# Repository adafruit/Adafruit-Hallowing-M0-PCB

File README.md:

## Adafruit HalloWing M0 Express PCB

<a href="http://www.adafruit.com/products/3900"><br/>
Click here to purchase one from the Adafruit shop</a>

PCB files for the Adafruit HalloWing M0 Express. Format is EagleCAD schematic and board layout
* https://www.adafruit.com/product/3900

### Description
[This is Hallowing..this is Hallowing... Hallowing! Hallowing!](https://www.youtube.com/watch?v=kGiYxCUAhks&t=39s)
Are you the kind of person who doesn't like taking down the skeletons and spiders until after January? Well, we've got the development board for you. This is electronics at its most spooky! The **Adafruit HalloWing** is a skull-shaped ATSAMD21 board with a ton of extras built in to make for an adorable wearable, badge, development kit, or the engine for your next cosplay or prop.

On the front is a cute **1.44" sized 128x128** full color TFT. Our default example code has our spooky eye demo running but you can use it for anything you like to display in glorious color.

There's also 4 fang-teeth below the display, these are analog/capacitive touch inputs with big alligator-clip holes.

On the reverse is a smorgasbord of electronic goodies:

 * **ATSAMD21G18** @ 48MHz with 3.3V logic/power - 256KB of FLASH + 32KB of RAM
 * **8 MB of SPI Flash** for storing images, sounds, animations, whatever!
 * **3-axis accelerometer** (motion sensor)
 * **Light sensor**, reverse-mount so that it points out the front
 * **Mono Class-D speaker driver** for 4-8 ohm speakers, up to 2 Watts, with mini volume pot
 * LiPoly battery port with built in recharging capability
 * USB port for battery charging, programming and debugging
 * Two female header strips with Feather-compatible pinout so you can plug any FeatherWings in
 * JST ports for Neopixels, sensor input, and I2C (you can fit I2C Grove connectors in here)
 * 3.3V regulator with 500mA peak current output
 * Reset button
 * On-Off switch

**OK so technically it's more like a really tricked-out Feather M0 Express than a Wing but we simply could not resist the Hallowing pun.**

Right now you can use the Hallowing similarly Feather M0 Express, it's got the same chip although the pins have been rearranged. We've got both Arduino and CircuitPython build support for it so you can pick your favorite development language! The extra 8 MB of SPI Flash is great for sound effects projects where you want to play up to 3 minutes of WAV files.

On each side of the Hallowing are JST-PH plugs for connecting external devices. The 3-pin JSTs connect to analog pins on the SAMD21, so you can use them for analog inputs. We label one for Neopixel and one for Sensors since we think most people will have one of each. The 4-pin JST connector connects to the I2C port and you can fit Grove connectors in it for additional hardware support.

**Does not come with a Lipoly battery!** [We recommend our 350mAh](https://www.adafruit.com/product/2750) or [500mAh batteries](https://www.adafruit.com/product/1578) but any 3.7/4.2V Adafruit Lipoly will do the trick.

Comes fully assembled and ready to be your spooky friend. We install the UF2 bootloader on it so updating code and converting it to CircuitPython is easy. [Check out the Adafruit Learn guide for software, libraries, example code, schematics, datasheets and more!](https://learn.adafruit.com/adafruit-hallowing)

### License

Adafruit invests time and resources providing this open source design, please support Adafruit and open-source hardware by purchasing products from [Adafruit](https://www.adafruit.com)!

Designed by Limor Fried/Ladyada for Adafruit Industries.

Creative Commons Attribution/Share-Alike, all text above must be included in any redistribution. See license.txt for additional details.

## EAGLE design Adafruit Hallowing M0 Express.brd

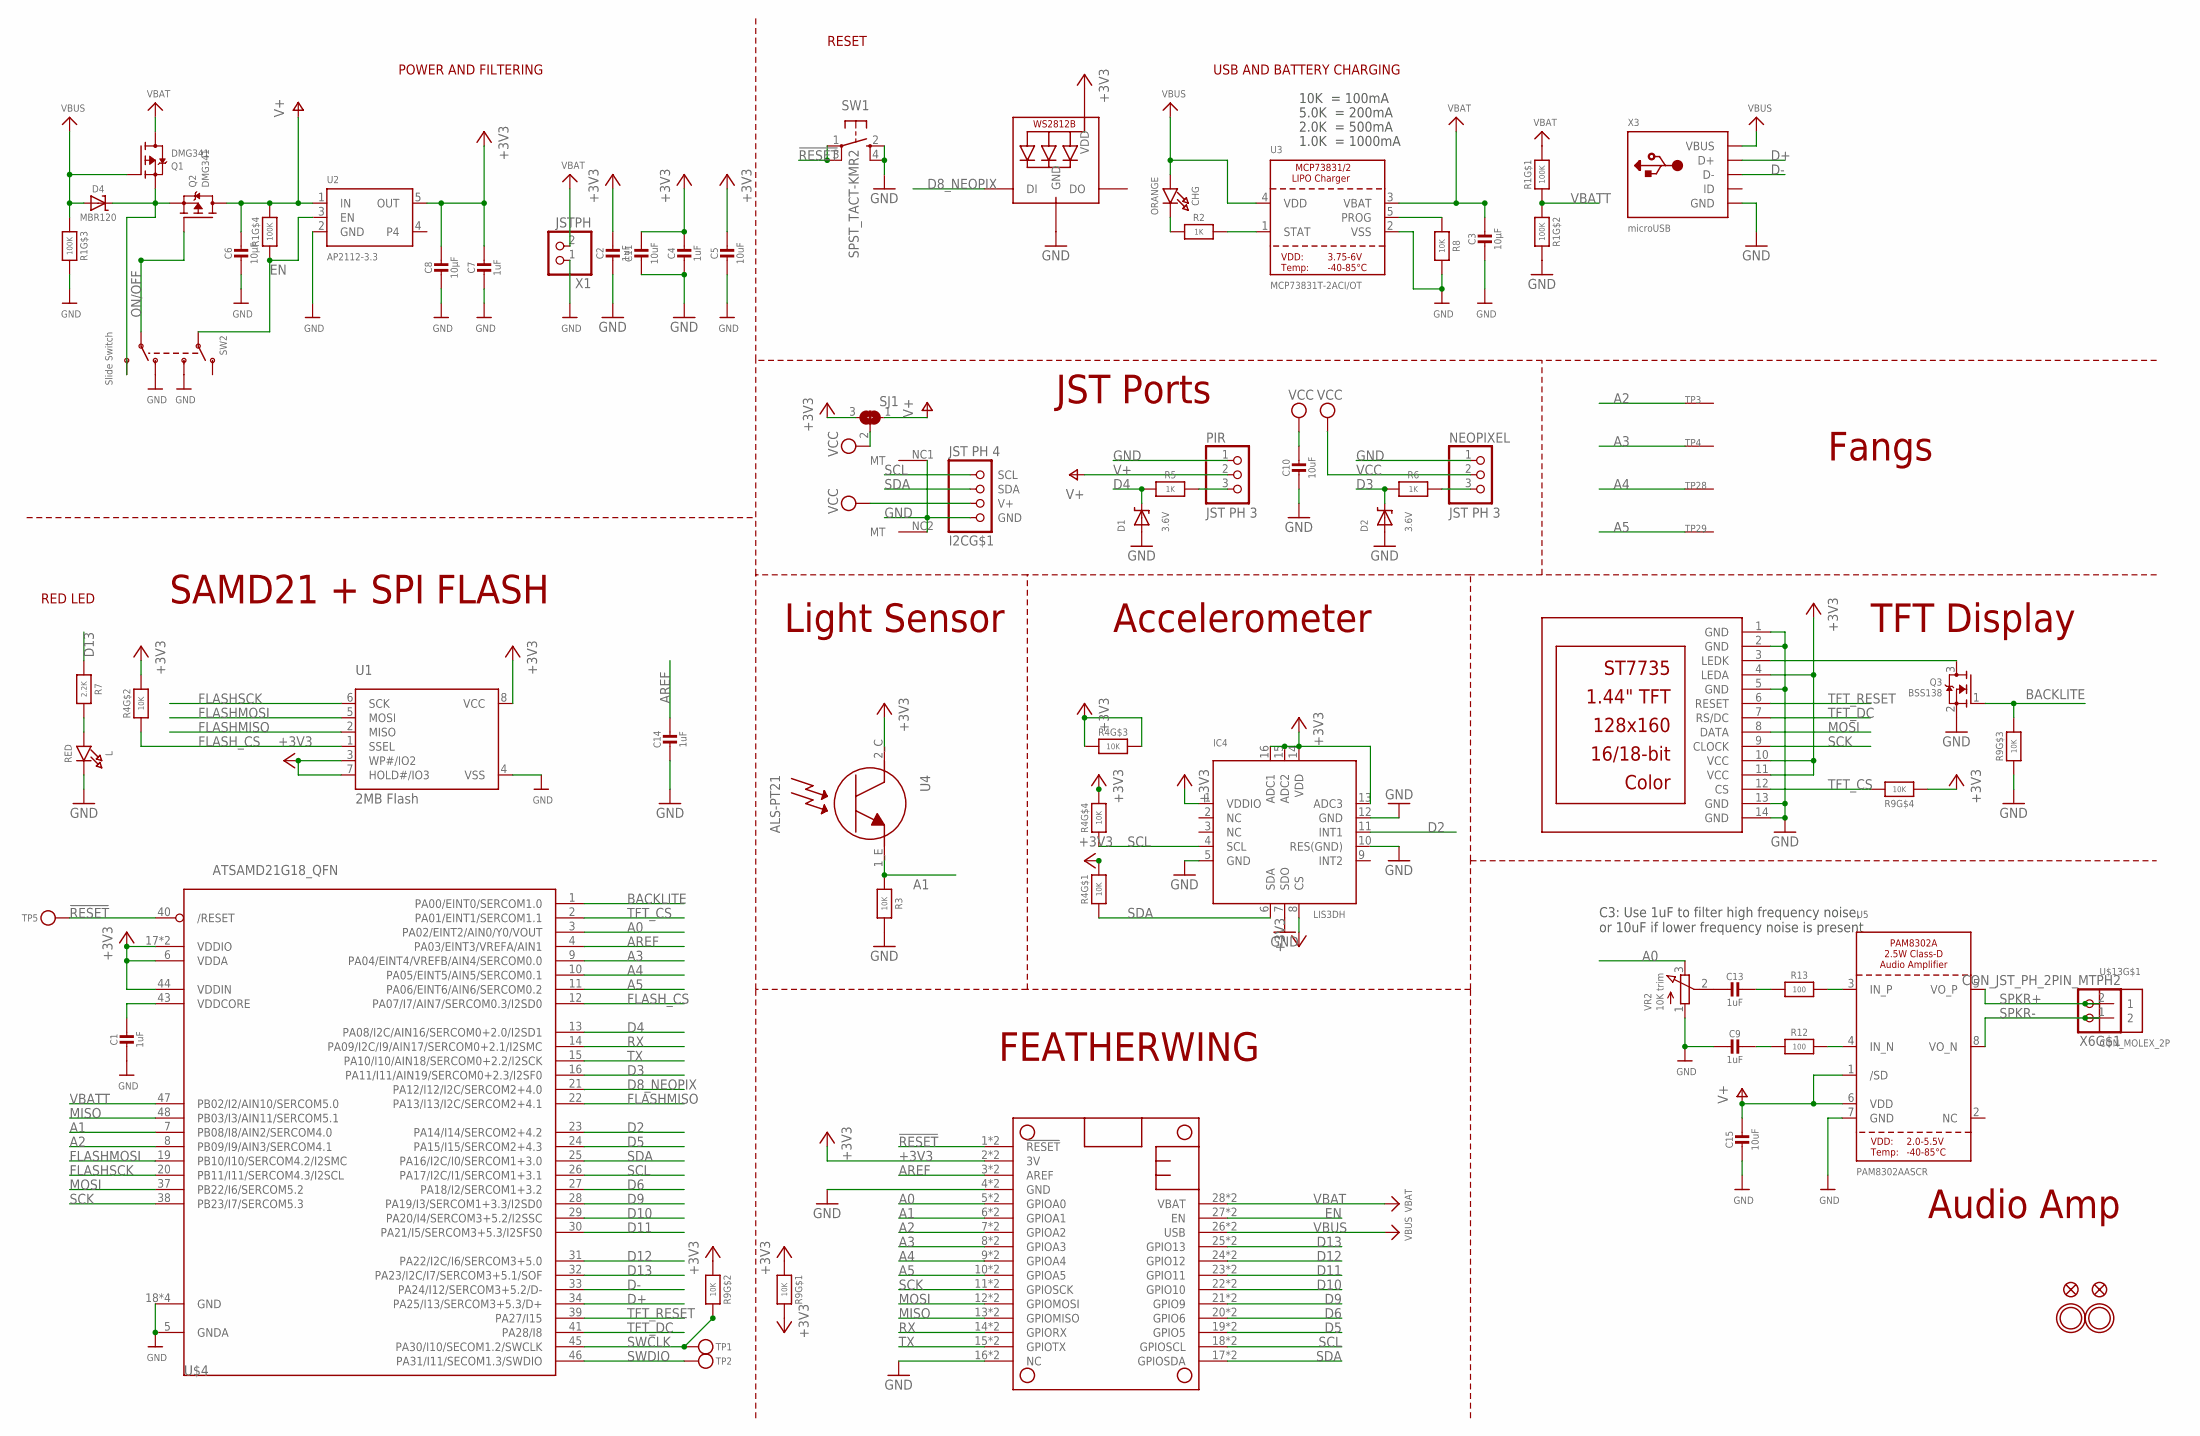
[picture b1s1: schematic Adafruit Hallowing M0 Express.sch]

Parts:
C1, C2, C4, C7, C9, C13, C14: 1uF; 0603-NO
C3, C6: 10µF; 0805-NO
C5, C10, C15: 10uF; 0805-NO
C8: 10µF; 0805_10MGAP
C11: 10uF; 0805_10MGAP
CHG: ORANGE; CHIPLED_0805_NOOUTLINE
D1, D2: 3.6V; SOD-323
D4: MBR120; SOD-123
I2C: JST PH 4; JSTPH4
IC4: LIS3DH; LGA16_3X3MM
L: RED; CHIPLED_0805_NOOUTLINE
LED1: WS2812B3535; LED3535
MS1: FEATHERWING_SMTDUALNOHOLES; FEATHERWING_SMT_NOHOLES
NEOPIXEL: JST PH 3; JSTPH3
PIR: JST PH 3; JSTPH3
Q1, Q2: DMG341; SOT23-R
Q3: BSS138; SOT23-WIDE
R1: 100K; RESPACK_4X0603
R2, R5, R6: 1K; 0603-NO
R3, R8: 10K; 0603-NO
R4, R9: 10K; RESPACK_4X0603
R7: 2.2K; 0603-NO
R12, R13: 100; 0603-NO
SJ1: SOLDERJUMPER_2WAY; SOLDERJUMPER_2WAY_OPEN_NOPASTE
SW1: SPST_TACT-KMR2; KMR2
SW2: Slide Switch; EG1390
TFT: DISP_LCD_ST7735_1.44IN; TFT_1.44IN_128_128
TP1, TP2, TP5: TESTPOINTROUND1.5MM; TESTPOINT_ROUND_1.5MM
TP3, TP29: SEWTAP_ALLILONG; PCB_ALLI_LONG
TP4, TP28: SEWTAPPCB_ALLIGATOR; PCB_ALLI
U1: 2MB Flash; SOIC8_208MIL
U2: AP2112-3.3; SOT23-5
U3: MCP73831T-2ACI/OT; SOT23-5
U4: ALS-PT21; ALS-PT26-21C
U5: PAM8302AASCR; MSOP8_0.65MM
U$4: ATSAMD21G18_QFN; TQFN48_7MM
U$13: CON_MOLEX_2P; 53398-0271
U$31, U$32: MOUNTINGHOLE2.5; MOUNTINGHOLE_2.5_PLATED
U$34, U$35: FIDUCIAL_1MM
VR2: 10K trim; TRIMPOT_BOURNS_3303W
X1: JSTPH; JSTPH2
X3: microUSB; 4UCONN_20329_V2
X6: CON_JST_PH_2PIN_MTPH2; JSTPH2

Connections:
!RESET: MS1.1 (!RESET), MS1.1' (!RESET), SW1.1, SW1.3 (P1), TP5.P$1, U$4.40 (/RESET)
+3V3: C2.1, C4.1, C5.1, C7.1, C8.1, C11.1, IC4.1 (VDDIO), IC4.8 (CS), IC4.13 (ADC3), IC4.14 (VDD), IC4.15 (ADC2), IC4.16 (ADC1), LED1.2 (VDD), MS1.2 (3V), MS1.2' (3V), R4.3 (1), R4.5 (2), R4.6 (2), R4.7 (2), R4.8 (2), R9.1, R9.2 (1), R9.4 (1), R9.8 (2), SJ1.3, TFT.4 (LEDA), TFT.10 (VCC), TFT.11 (VCC), U1.3 (WP#/IO2), U1.7 (HOLD#/IO3), U1.8 (VCC), U2.5 (OUT), U4.2_C (C), U$4.6 (VDDA), U$4.17 (VDDIO), U$4.36 (VDDIO), U$4.44 (VDDIN)
A0: MS1.5 (GPIOA0), MS1.5' (GPIOA0), U$4.3 (PA02/EINT2/AIN0/Y0/VOUT), VR2.3 (E)
A1: MS1.6 (GPIOA1), MS1.6' (GPIOA1), R3.2, U4.1_E (E), U$4.7 (PB08/I8/AIN2/SERCOM4.0)
A2: MS1.7 (GPIOA2), MS1.7' (GPIOA2), TP3.P$1, U$4.8 (PB09/I9/AIN3/SERCOM4.1)
A3: MS1.8 (GPIOA3), MS1.8' (GPIOA3), TP4.P$1, U$4.9 (PA04/EINT4/VREFB/AIN4/SERCOM0.0)
A4: MS1.9 (GPIOA4), MS1.9' (GPIOA4), TP28.P$1, U$4.10 (PA05/EINT5/AIN5/SERCOM0.1)
A5: MS1.10 (GPIOA5), MS1.10' (GPIOA5), TP29.P$1, U$4.11 (PA06/EINT6/AIN6/SERCOM0.2)
AREF: C14.1, MS1.3 (AREF), MS1.3' (AREF), U$4.4 (PA03/EINT3/VREFA/AIN1)
BACKLITE: Q3.1 (G), R9.6 (2), U$4.1 (PA00/EINT0/SERCOM1.0)
CHG_LED: R2.2, U3.1 (STAT)
CHG_RATE: R8.1, U3.5 (PROG)
D2: IC4.11 (INT1), U$4.23 (PA14/I14/SERCOM2+4.2)
D3: D2.C, R6.2, U$4.16 (PA11/I11/AIN19/SERCOM0+2.3/I2SF0)
D4: D1.C, R5.2, U$4.13 (PA08/I2C/AIN16/SERCOM0+2.0/I2SD1)
D5: MS1.19 (GPIO5), MS1.19' (GPIO5), U$4.24 (PA15/I15/SERCOM2+4.3)
D6: MS1.20 (GPIO6), MS1.20' (GPIO6), U$4.27 (PA18/I2/SERCOM1+3.2)
D8_NEOPIX: LED1.1 (DI), U$4.21 (PA12/I12/I2C/SERCOM2+4.0)
D9: MS1.21 (GPIO9), MS1.21' (GPIO9), U$4.28 (PA19/I3/SERCOM1+3.3/I2SD0)
D10: MS1.22 (GPIO10), MS1.22' (GPIO10), U$4.29 (PA20/I4/SERCOM3+5.2/I2SSC)
D11: MS1.23 (GPIO11), MS1.23' (GPIO11), U$4.30 (PA21/I5/SERCOM3+5.3/I2SFS0)
D12: MS1.24 (GPIO12), MS1.24' (GPIO12), U$4.31 (PA22/I2C/I6/SERCOM3+5.0)
D13: MS1.25 (GPIO13), MS1.25' (GPIO13), R7.1, U$4.32 (PA23/I2C/I7/SERCOM3+5.1/SOF)
D+: U$4.34 (PA25/I13/SERCOM3+5.3/D+), X3.D+
D-: U$4.33 (PA24/I12/SERCOM3+5.2/D-), X3.D-
EN: MS1.27 (EN), MS1.27' (EN), R1.4 (1), SW2.P1, U2.3 (EN)
FLASHMISO: U1.2 (MISO), U$4.22 (PA13/I13/I2C/SERCOM2+4.1)
FLASHMOSI: U1.5 (MOSI), U$4.19 (PB10/I10/SERCOM4.2/I2SMC)
FLASHSCK: U1.6 (SCK), U$4.20 (PB11/I11/SERCOM4.3/I2SCL)
FLASH_CS: R4.2 (1), U1.1 (SSEL), U$4.12 (PA07/I7/AIN7/SERCOM0.3/I2SD0)
GND: C1.2, C2.2, C3.2, C4.2, C5.2, C6.2, C7.2, C8.2, C9.2, C10.2, C11.2, C14.2, C15.2, D1.A, D2.A, I2C.1 (GND), I2C.NC1 (MT), I2C.NC2 (MT), IC4.5 (GND), IC4.7 (SDO), IC4.10 (RES(GND)), IC4.12 (GND), L.C, LED1.4 (GND), MS1.4 (GND), MS1.4' (GND), MS1.16 (NC), MS1.16' (NC), NEOPIXEL.1, PIR.1, Q3.2 (S), R1.6 (2), R1.7 (2), R3.1, R8.2, R9.3 (1), SW1.2 (S), SW1.4 (S1), SW2.O2, SW2.S1, TFT.1 (GND), TFT.2 (GND), TFT.5 (GND), TFT.13 (GND), TFT.14 (GND), U1.4 (VSS), U2.2 (GND), U3.2 (VSS), U5.7 (GND), U$4.5 (GNDA), U$4.18 (GND), U$4.35 (GND), U$4.42 (GND), U$4.THERMAL (GND), VR2.1 (A), X1.1, X3.BASE@1 (GND), X3.BASE@2 (GND), X3.GND, X3.SPRT@1 (GND), X3.SPRT@2 (GND), X3.SPRT@3 (GND), X3.SPRT@4 (GND)
MISO: MS1.13 (GPIOMISO), MS1.13' (GPIOMISO), U$4.48 (PB03/I3/AIN11/SERCOM5.1)
MOSI: MS1.12 (GPIOMOSI), MS1.12' (GPIOMOSI), TFT.8 (DATA), U$4.37 (PB22/I6/SERCOM5.2)
unnamed: CHG.C, R2.1
unnamed: L.A, R7.2
unnamed: Q3.3 (D), TFT.3 (LEDK)
unnamed: D4.C, Q1.2 (S), Q2.2 (S), SW2.S2
unnamed: R12.2, U5.4 (IN_N)
unnamed: R13.2, U5.3 (IN_P)
unnamed: C9.1, R12.1
unnamed: C13.1, R13.1
unnamed: C13.2, VR2.2 (S)
NEOPIXELOUT: NEOPIXEL.3, R6.1
ON/OFF: Q2.1 (G), SW2.P2
RX: MS1.14 (GPIORX), MS1.14' (GPIORX), U$4.14 (PA09/I2C/I9/AIN17/SERCOM0+2.1/I2SMC)
SCK: MS1.11 (GPIOSCK), MS1.11' (GPIOSCK), TFT.9 (CLOCK), U$4.38 (PB23/I7/SERCOM5.3)
SCL: I2C.4 (SCL), IC4.4 (SCL), MS1.18 (GPIOSCL), MS1.18' (GPIOSCL), R4.4 (1), U$4.26 (PA17/I2C/I1/SERCOM1+3.1)
SDA: I2C.3 (SDA), IC4.6 (SDA), MS1.17 (GPIOSDA), MS1.17' (GPIOSDA), R4.1, U$4.25 (PA16/I2C/I0/SERCOM1+3.0)
SENSORIN: PIR.3, R5.1
SPKR+: U5.5 (VO_P), U$13.1, X6.2
SPKR-: U5.8 (VO_N), U$13.2, X6.1
SWCLK: R9.7 (2), TP1.P$1, U$4.45 (PA30/I10/SECOM1.2/SWCLK)
SWDIO: TP2.P$1, U$4.46 (PA31/I11/SECOM1.3/SWDIO)
TFT_CS: R9.5 (2), TFT.12 (CS), U$4.2 (PA01/EINT1/SERCOM1.1)
TFT_DC: TFT.7 (RS/DC), U$4.41 (PA28/I8)
TFT_RESET: TFT.6 (RESET), U$4.39 (PA27/I15)
TX: MS1.15 (GPIOTX), MS1.15' (GPIOTX), U$4.15 (PA10/I10/AIN18/SERCOM0+2.2/I2SCK)
V+: C6.1, C15.1, PIR.2, Q2.3 (D), R1.5 (2), SJ1.1, U2.1 (IN), U5.1 (/SD), U5.6 (VDD)
VBAT: C3.1, MS1.28 (VBAT), MS1.28' (VBAT), Q1.3 (D), R1.8 (2), U3.3 (VBAT), X1.2
VBATT: R1.1, R1.2 (1), U$4.47 (PB02/I2/AIN10/SERCOM5.0)
VBUS: CHG.A, D4.A, MS1.26 (USB), MS1.26' (USB), Q1.1 (G), R1.3 (1), U3.4 (VDD), X3.VBUS
VCC: C10.1, I2C.2 (V+), NEOPIXEL.2, SJ1.2
VDDCORE: C1.1, U$4.43 (VDDCORE)

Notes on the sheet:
POWER AND FILTERING
RESET
10K = 100mA
5.0K = 200mA
2.0K = 500mA
1.0K = 1000mA
USB AND BATTERY CHARGING
RED LED
C3: Use 1uF to filter high frequency noise, or 10uF if lower frequency noise is present
Accelerometer
Light Sensor
FEATHERWING
SAMD21 + SPI FLASH
Fangs
TFT Display
Audio Amp
JST Ports

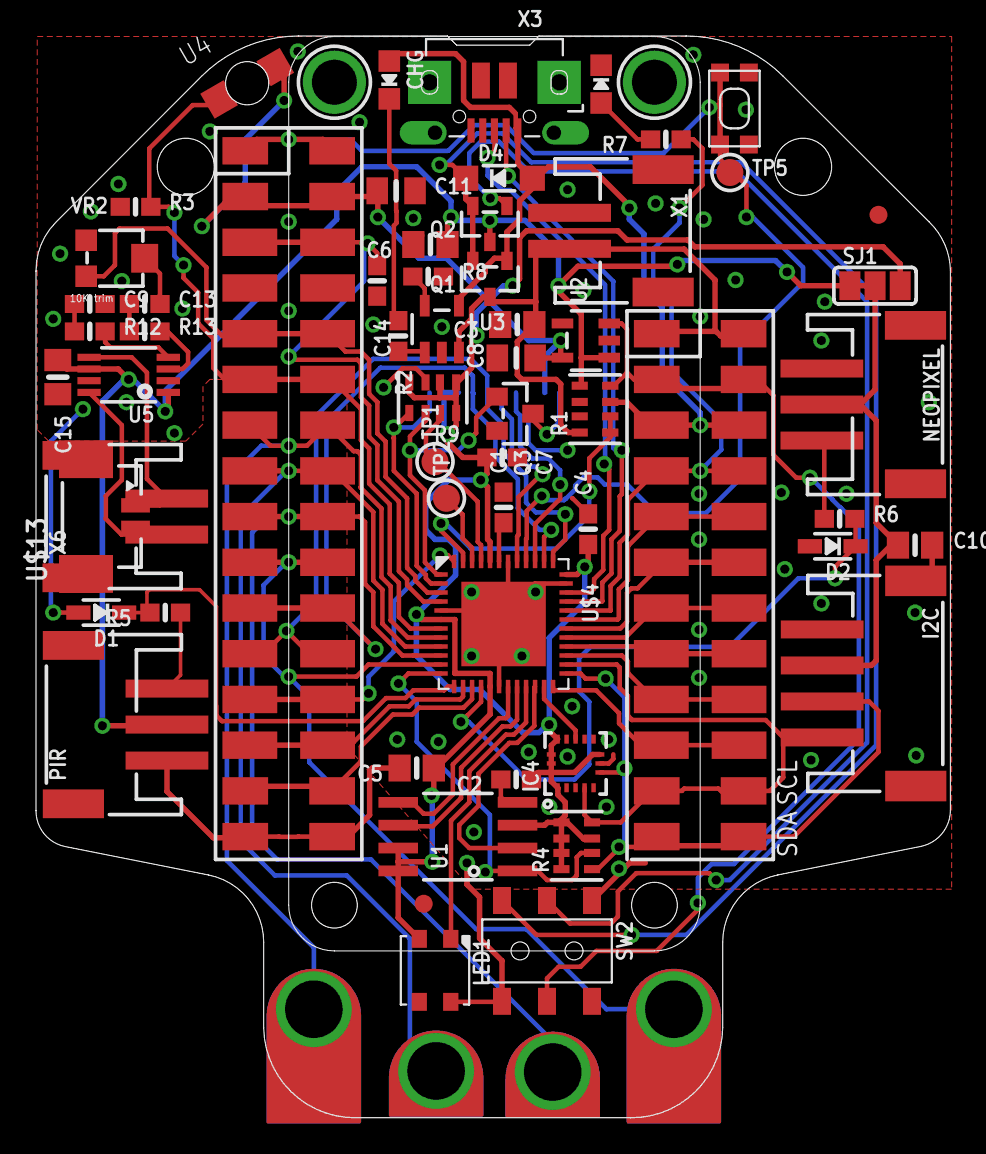
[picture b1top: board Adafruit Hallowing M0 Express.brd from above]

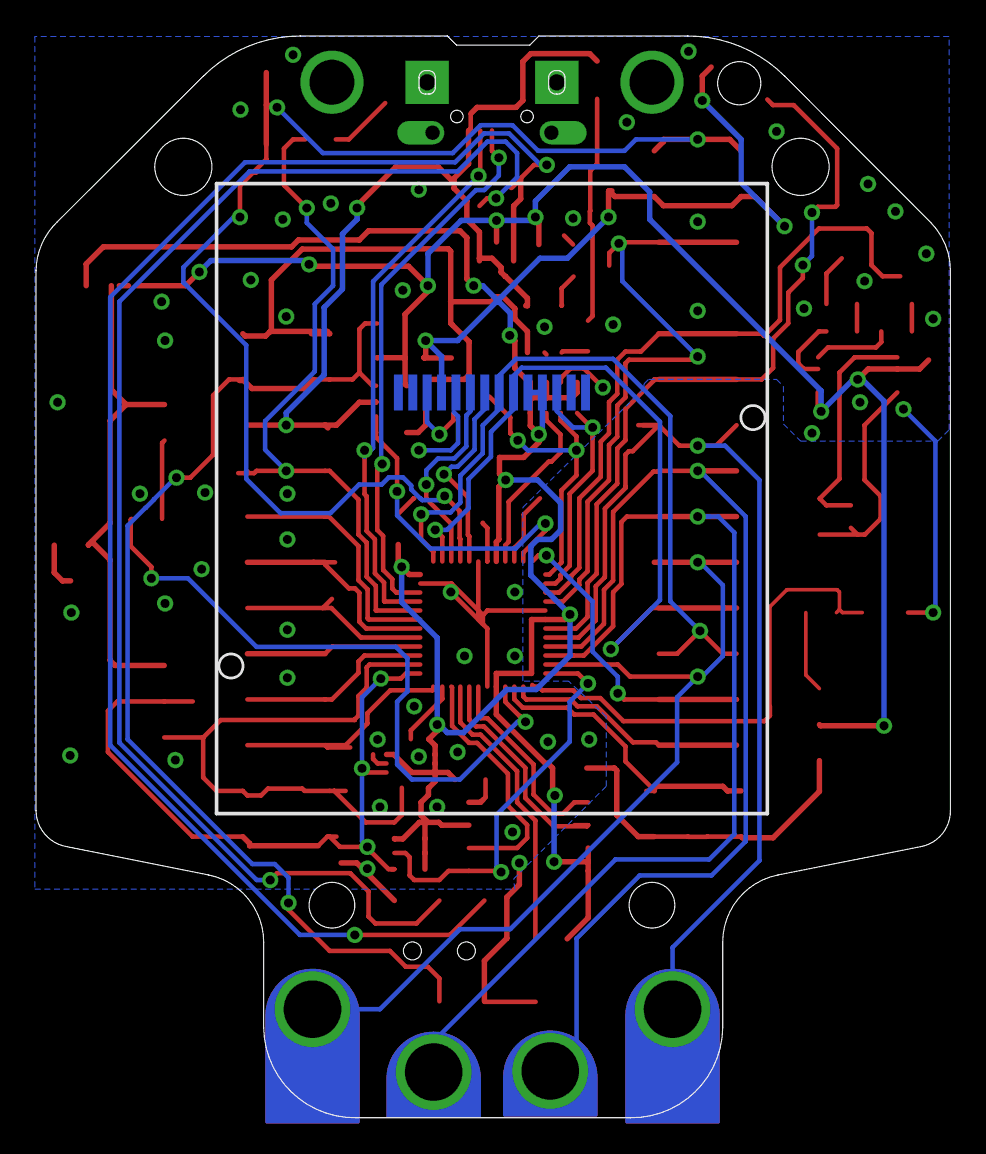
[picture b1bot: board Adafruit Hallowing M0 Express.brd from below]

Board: 2 copper layers, 50.8 x 60.1 mm, 67 parts (2 on the bottom side), 63 nets.

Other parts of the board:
U$8: HALLOWING_BACK
U$12: HALLOWING_FRONT

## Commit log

2018-08-15 boo!
2018-09-11 lens holder
2019-07-16 updated to use the new pcb repo cookiecutter
2019-07-16 typo fix
2021-05-18 Add pinout PDF

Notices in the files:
parts and their libraries:
microbuilder: This work is placed in the public domain, and may be freely used for commercial and non-commercial work with the following conditions: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
